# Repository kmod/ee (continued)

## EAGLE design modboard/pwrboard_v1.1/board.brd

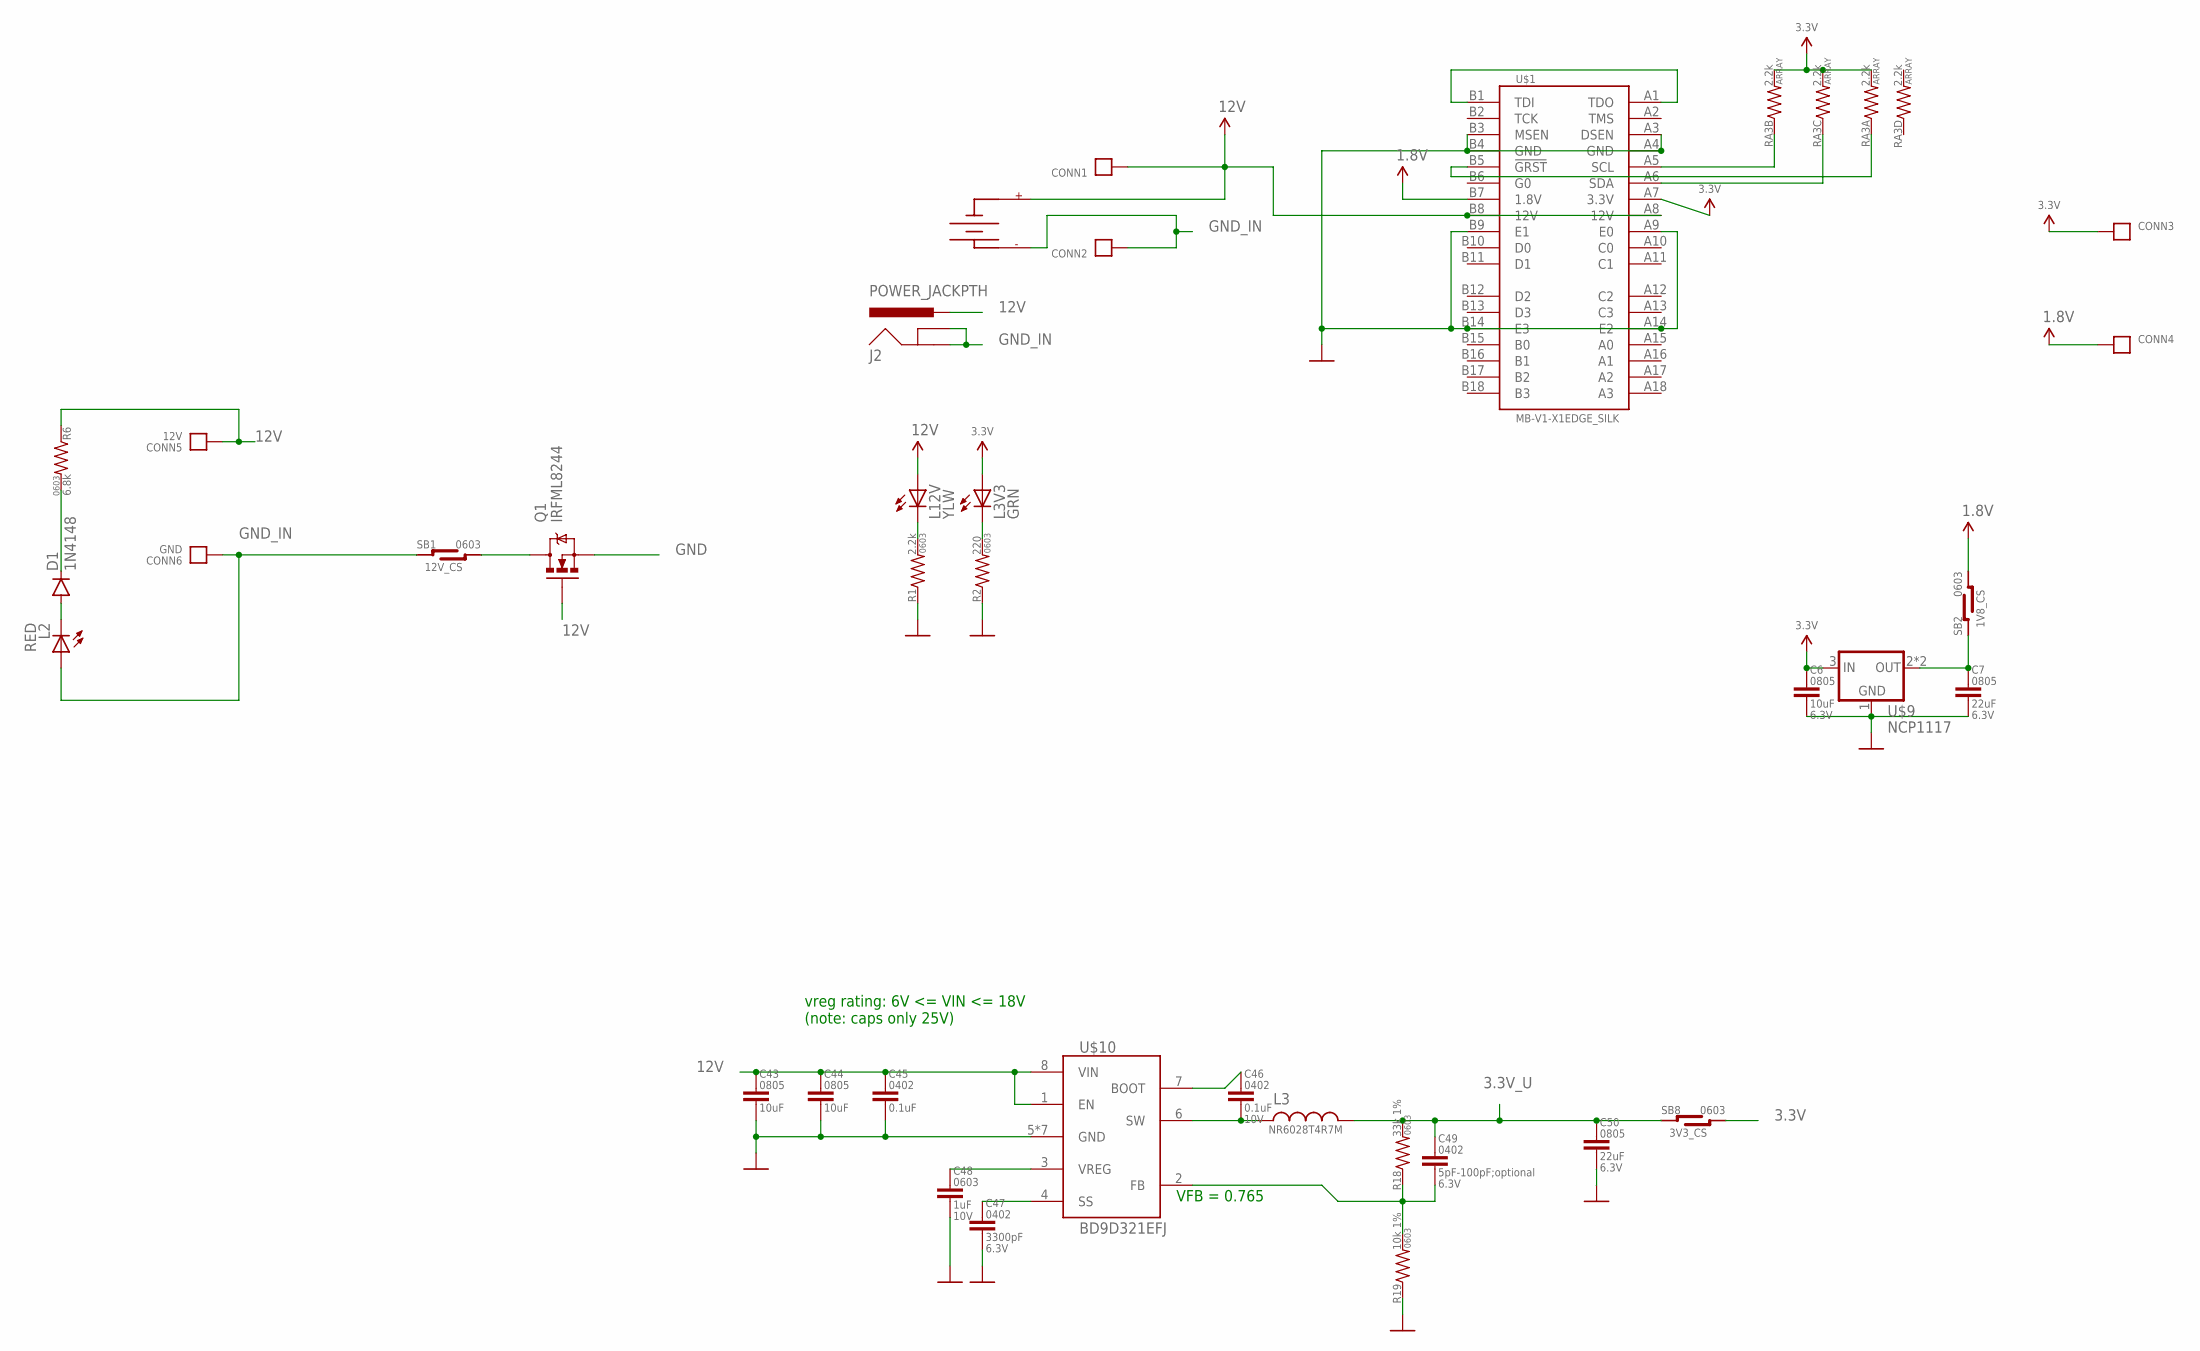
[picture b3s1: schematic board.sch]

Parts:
C6: 10uF; 0805-CAP
C7, C50: 22uF; 0805-CAP
C43, C44: 10uF; 0805-CAP; VOLTAGE 25V
C45: 0.1uF; 0402-CAP; VOLTAGE 25V
C46: 0.1uF; 0402-CAP; VOLTAGE 10V
C47: 3300pF; 0402-CAP
C48: 1uF; 0603-CAP; VOLTAGE 10V
C49: 5pF-100pF;optional; 0402-CAP
CONN1, CONN2, CONN3, CONN4: CONNECTOR18AWG; HOLE_18AWG
CONN5: 12V; SCREW_2.5MM
CONN6: GND; SCREW_2.5MM
D1: 1N4148; SOD-323
J2: POWER_JACKPTH; POWER_JACK_PTH
L2: RED; 0603_LED
L3: NR6028T4R7M; NR60XX
L3V3: GRN; 0603_LED
L12V: YLW; 0603_LED
Q1: IRFML8244; SOT23
R1: 2.2k; 0603-RES
R2: 220; 0603-RES
R6: 6.8k; 0603-RES
R18: 33k 1%; 0603-RES
R19: 10k 1%; 0603-RES
RA3: 2.2k; 0603-ARV
SB1: 12V_CS; SB-0603
SB2: 1V8_CS; SB-0603
SB8: 3V3_CS; SB-0603
U$1: MB-V1-X1EDGE_SILK; MB-V1-X1-EDGE
U$4: SUPPLYPCIE-6-RA; MOLEX_MINIFITJR_6_RA
U$9: NCP1117; SOT223
U$10: BD9D321EFJ; HTSOP8

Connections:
1.8V: CONN4.P$1, SB2.R1, SB2.R2, U$1.B7 (1.8V)
3.3V: C6.1, CONN3.P$1, L3V3.A, RA3.6 (2), RA3.7 (2), RA3.8 (2), SB8.R1, SB8.R2, U$1.A7 (3.3V), U$9.3 (IN)
3.3V_FB: C49.2, R18.1, R19.2, U$10.2 (FB)
3.3V_U: C49.1, C50.1, L3.P$2 (2), R18.2, SB8.L1, SB8.L2
12V: C43.1, C44.1, C45.1, CONN1.P$1, CONN5.P, J2.PWR, L12V.A, Q1.1 (G), R6.1, U$1.A8 (12V), U$1.B8 (12V), U$4.1 (VSUPPLY), U$4.3 (VSUPPLY), U$10.1 (EN), U$10.8 (VIN)
GND: C6.2, C7.2, C43.2, C44.2, C45.2, C47.2, C48.2, C50.2, Q1.2 (S), R1.1, R2.1, R19.1, U$1.A3 (DSEN), U$1.A4 (GND), U$1.A9 (E0), U$1.A14 (E2), U$1.B3 (MSEN), U$1.B4 (GND), U$1.B9 (E1), U$1.B14 (E3), U$9.1 (GND), U$10.5 (GND), U$10.P$1 (GND), U$10.P$2 (GND), U$10.P$3 (GND), U$10.P$4 (GND), U$10.P$5 (GND), U$10.PAD (GND)
GND_IN: CONN2.P$1, CONN6.P, J2.GND, J2.GNDBREAK, L2.A, SB1.L1, SB1.L2, U$4.4 (GND), U$4.6 (GND)
unnamed: L12V.C, R1.2
unnamed: C7.1, SB2.L1, SB2.L2, U$9.2 (OUT), U$9.4 (OUT)
unnamed: L3V3.C, R2.2
unnamed: RA3.3 (1), U$1.A6 (SDA)
unnamed: Q1.3 (D), SB1.R1, SB1.R2
unnamed: D1.C, R6.2
unnamed: RA3.2 (1), U$1.A5 (SCL)
unnamed: RA3.1, U$1.B5 (!GRST)
unnamed: D1.A, L2.C
unnamed: C46.2, L3.P$1 (1), U$10.6 (SW)
unnamed: C46.1, U$10.7 (BOOT)
unnamed: C48.1, U$10.3 (VREG)
unnamed: C47.1, U$10.4 (SS)
TDI: U$1.A1 (TDO), U$1.B1 (TDI)

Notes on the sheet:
VFB = 0.765
vreg rating: 6V <= VIN <= 18V (note: caps only 25V)

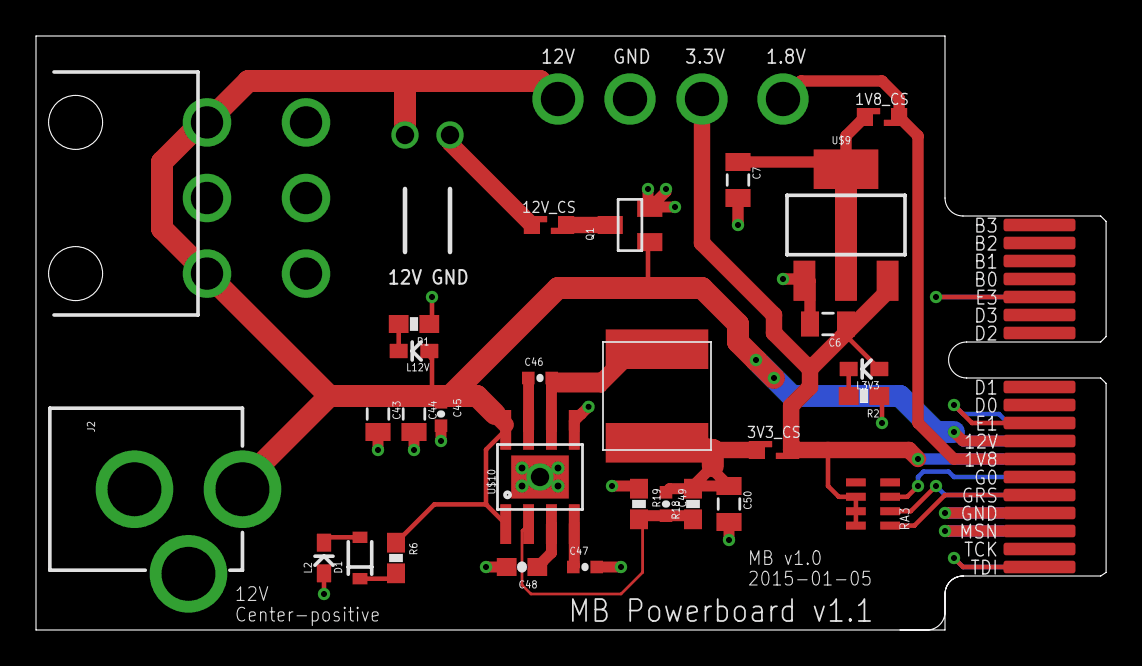
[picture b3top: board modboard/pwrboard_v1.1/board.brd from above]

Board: 2 copper layers, 59.4 x 33.0 mm, 36 parts (0 on the bottom side), 21 nets.

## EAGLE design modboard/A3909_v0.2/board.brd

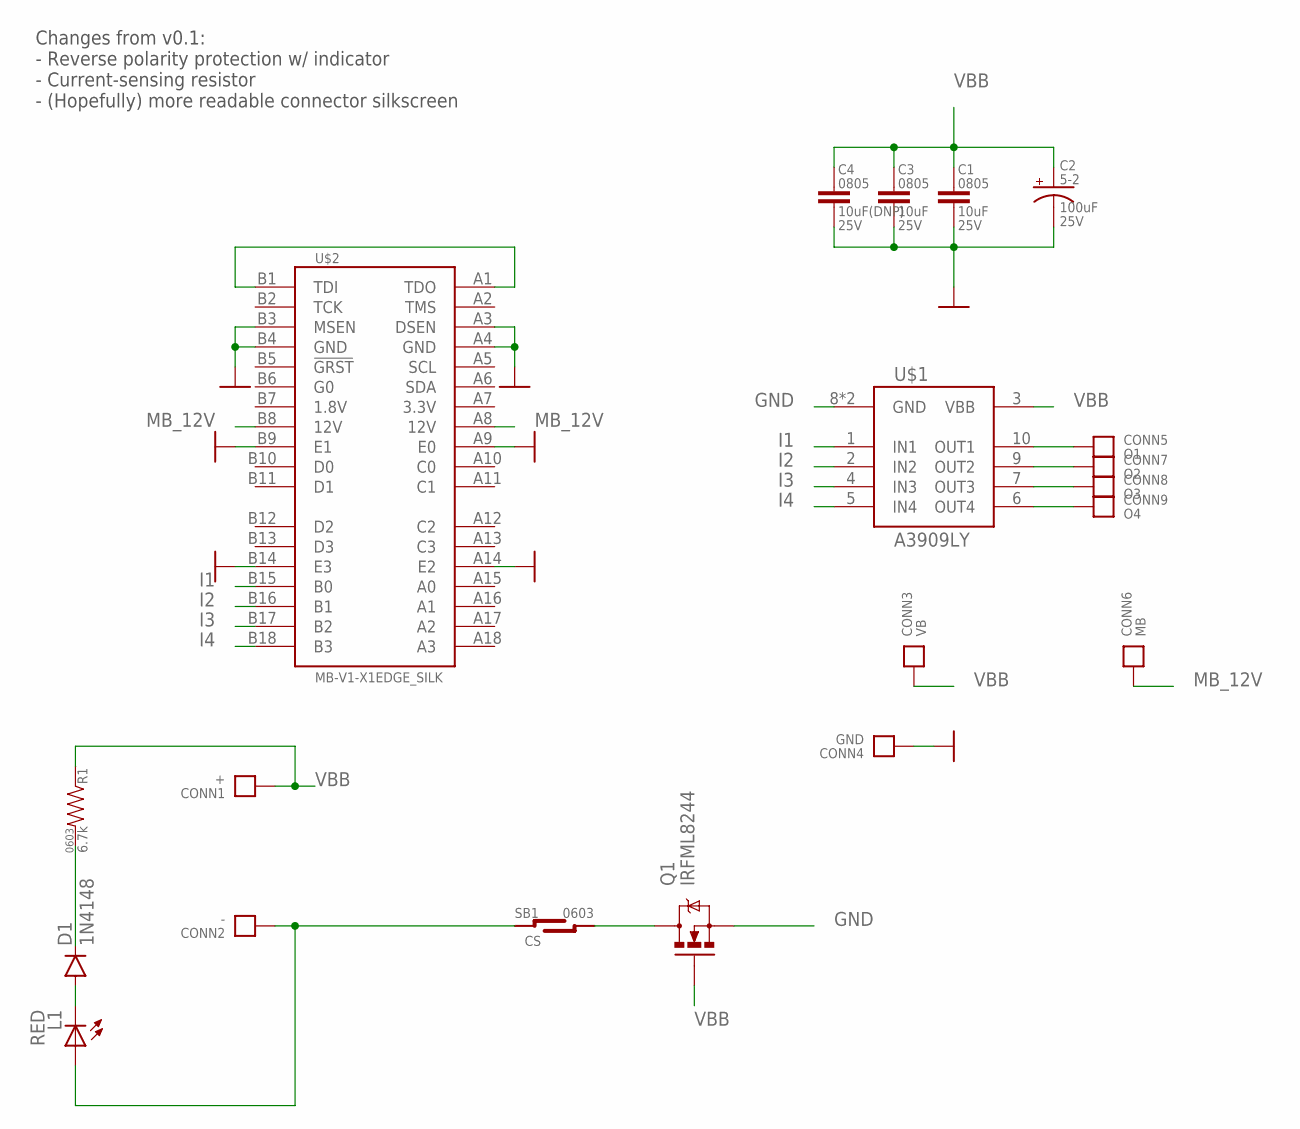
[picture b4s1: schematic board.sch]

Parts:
C1, C3: 10uF; 0805-CAP; VOLTAGE 25V
C2: 100uF; CAP-5-2; VOLTAGE 25V
C4: 10uF(DNP); 0805-CAP; VOLTAGE 25V
CONN1: +; SCREW_5MM
CONN2: -; SCREW_5MM
CONN3: VB; SCREW_2.5MM
CONN4: GND; SCREW_2.5MM
CONN5: O1; SCREW_2.5MM
CONN6: MB; SCREW_2.5MM
CONN7: O2; SCREW_2.5MM
CONN8: O3; SCREW_2.5MM
CONN9: O4; SCREW_2.5MM
D1: 1N4148; SOD-323
L1: RED; 0603_LED
Q1: IRFML8244; SOT23
R1: 6.7k; 0603-RES
SB1: CS; SB-0603
U$1: A3909LY; MSOP10
U$2: MB-V1-X1EDGE_SILK; MB-V1-X1-EDGE

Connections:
GND: C1.2, C2.2 (-), C3.2, C4.2, CONN4.P, Q1.2 (S), U$1.8 (GND), U$1.PAD (GND), U$2.A3 (DSEN), U$2.A4 (GND), U$2.A9 (E0), U$2.A14 (E2), U$2.B3 (MSEN), U$2.B4 (GND), U$2.B9 (E1), U$2.B14 (E3)
I1: U$1.1 (IN1), U$2.B15 (B0)
I2: U$1.2 (IN2), U$2.B16 (B1)
I3: U$1.4 (IN3), U$2.B17 (B2)
I4: U$1.5 (IN4), U$2.B18 (B3)
MB_12V: CONN6.P, U$2.A8 (12V), U$2.B8 (12V)
unnamed: U$2.A1 (TDO), U$2.B1 (TDI)
unnamed: D1.A, L1.C
unnamed: CONN2.P$1, L1.A, SB1.L1, SB1.L2
unnamed: Q1.3 (D), SB1.R1, SB1.R2
unnamed: D1.C, R1.2
O1: CONN5.P, U$1.10 (OUT1)
O2: CONN7.P, U$1.9 (OUT2)
O3: CONN8.P, U$1.7 (OUT3)
O4: CONN9.P, U$1.6 (OUT4)
VBB: C1.1, C2.1 (+), C3.1, C4.1, CONN1.P$1, CONN3.P, Q1.1 (G), R1.1, U$1.3 (VBB)

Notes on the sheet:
Changes from v0.1: - Reverse polarity protection w/ indicator - Current-sensing resistor - (Hopefully) more readable connector silkscreen

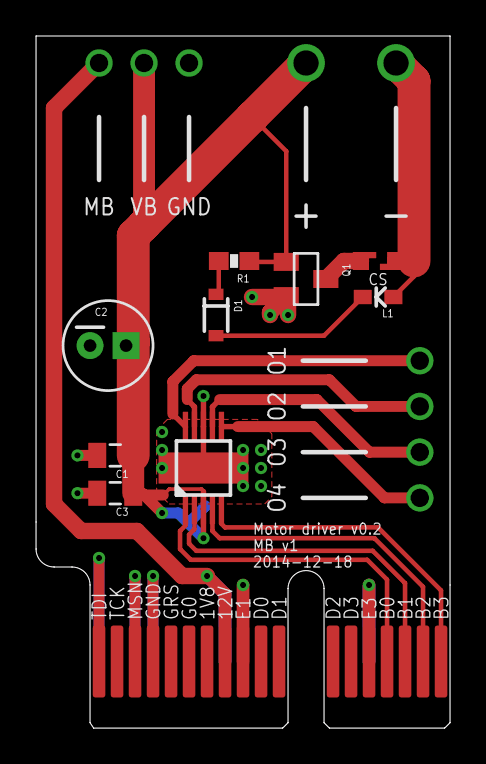
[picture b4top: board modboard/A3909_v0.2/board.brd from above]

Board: 2 copper layers, 23.0 x 38.4 mm, 20 parts (1 on the bottom side), 16 nets.

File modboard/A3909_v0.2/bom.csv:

"Qty";"Value";"Device";"Package";"Parts";"Description";"PACKAGE";"PROD_ID";"VOLTAGE";
"1";"+";"CONNECTORSCREW_5MM";"SCREW_5MM";"CONN1";"Collection of holes/pads for testing/connecting";"";"";"";
"1";"-";"CONNECTORSCREW_5MM";"SCREW_5MM";"CONN2";"Collection of holes/pads for testing/connecting";"";"";"";
"1";"100uF";"CAP_POLPTH-5-2";"CAP-5-2";"C2";"Capacitor Polarized";"5-2";"";"25V";
"2";"10uF";"CAP0805";"0805-CAP";"C1, C3";"Capacitor";"0805";"";"25V";
"1";"10uF(DNP)";"CAP0805";"0805-CAP";"C4";"Capacitor";"0805";"";"25V";
"1";"1N4148";"DIODESOD";"SOD-323";"D1";"Diode";"";"DIO-09646";"";
"1";"6.7k";"RESISTOR0603";"0603-RES";"R1";"Resistor";"0603";"";"";
"1";"A3909LY";"A3909LY";"MSOP10";"U$1";"A3909 Dual Fuul Bridge Motor Driver";"";"";"";
"1";"CS";"SOLDER-BRIDGE0603";"SB-0603";"SB1";"";"0603";"";"";
"1";"GND";"CONNECTORSCREW_2.5MM";"SCREW_2.5MM";"CONN4";"Collection of holes/pads for testing/connecting";"";"";"";
"1";"IRFML8244";"MOSFET-NCHANNELBSS138";"SOT23";"Q1";"Common NMOSFET Parts";"";"TRANS-00830";"";
"1";"MB";"CONNECTORSCREW_2.5MM";"SCREW_2.5MM";"CONN6";"Collection of holes/pads for testing/connecting";"";"";"";
"1";"MB-V1-X1EDGE_SILK";"MB-V1-X1EDGE_SILK";"MB-V1-X1-EDGE";"U$2";"";"";"";"";
"1";"O1";"CONNECTORSCREW_2.5MM";"SCREW_2.5MM";"CONN5";"Collection of holes/pads for testing/connecting";"";"";"";
"1";"O2";"CONNECTORSCREW_2.5MM";"SCREW_2.5MM";"CONN7";"Collection of holes/pads for testing/connecting";"";"";"";
"1";"O3";"CONNECTORSCREW_2.5MM";"SCREW_2.5MM";"CONN8";"Collection of holes/pads for testing/connecting";"";"";"";
"1";"O4";"CONNECTORSCREW_2.5MM";"SCREW_2.5MM";"CONN9";"Collection of holes/pads for testing/connecting";"";"";"";
"1";"RED";"LED0603";"0603_LED";"L1";"";"";"";"";
"1";"VB";"CONNECTORSCREW_2.5MM";"SCREW_2.5MM";"CONN3";"Collection of holes/pads for testing/connecting";"";"";"";

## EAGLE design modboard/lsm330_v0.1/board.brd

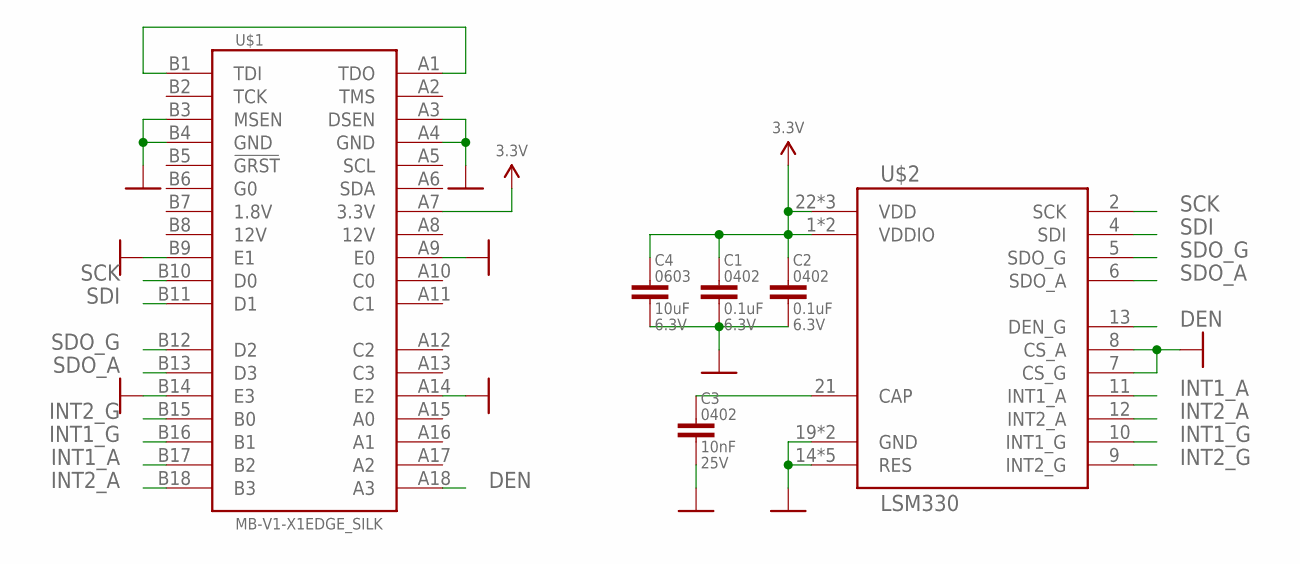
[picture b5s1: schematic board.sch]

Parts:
C1, C2: 0.1uF; 0402-CAP
C3: 10nF; 0402-CAP; VOLTAGE 25V
C4: 10uF; 0603-CAP
U$1: MB-V1-X1EDGE_SILK; MB-V1-X1-EDGE
U$2: LSM330

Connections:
3.3V: C1.1, C2.1, C4.1, U$1.A7 (3.3V), U$2.1 (VDDIO), U$2.3 (VDDIO), U$2.22 (VDD), U$2.23 (VDD), U$2.24 (VDD)
CAP: C3.1, U$2.21 (CAP)
DEN: U$1.A18 (A3), U$2.13 (DEN_G)
GND: C1.2, C2.2, C3.2, C4.2, U$1.A3 (DSEN), U$1.A4 (GND), U$1.A9 (E0), U$1.A14 (E2), U$1.B3 (MSEN), U$1.B4 (GND), U$1.B9 (E1), U$1.B14 (E3), U$2.7 (CS_G), U$2.8 (CS_A), U$2.14 (RES), U$2.15 (RES), U$2.16 (RES), U$2.17 (RES), U$2.18 (RES), U$2.19 (GND), U$2.20 (GND)
INT1_A: U$1.B17 (B2), U$2.11 (INT1_A)
INT1_G: U$1.B16 (B1), U$2.10 (INT1_G)
INT2_A: U$1.B18 (B3), U$2.12 (INT2_A)
INT2_G: U$1.B15 (B0), U$2.9 (INT2_G)
unnamed: U$1.A1 (TDO), U$1.B1 (TDI)
SCK: U$1.B10 (D0), U$2.2 (SCK)
SDI: U$1.B11 (D1), U$2.4 (SDI)
SDO_A: U$1.B13 (D3), U$2.6 (SDO_A)
SDO_G: U$1.B12 (D2), U$2.5 (SDO_G)

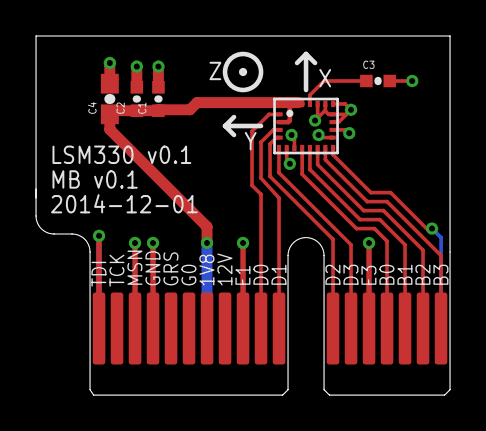
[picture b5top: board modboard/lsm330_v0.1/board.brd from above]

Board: 2 copper layers, 23.0 x 19.9 mm, 6 parts (0 on the bottom side), 13 nets.

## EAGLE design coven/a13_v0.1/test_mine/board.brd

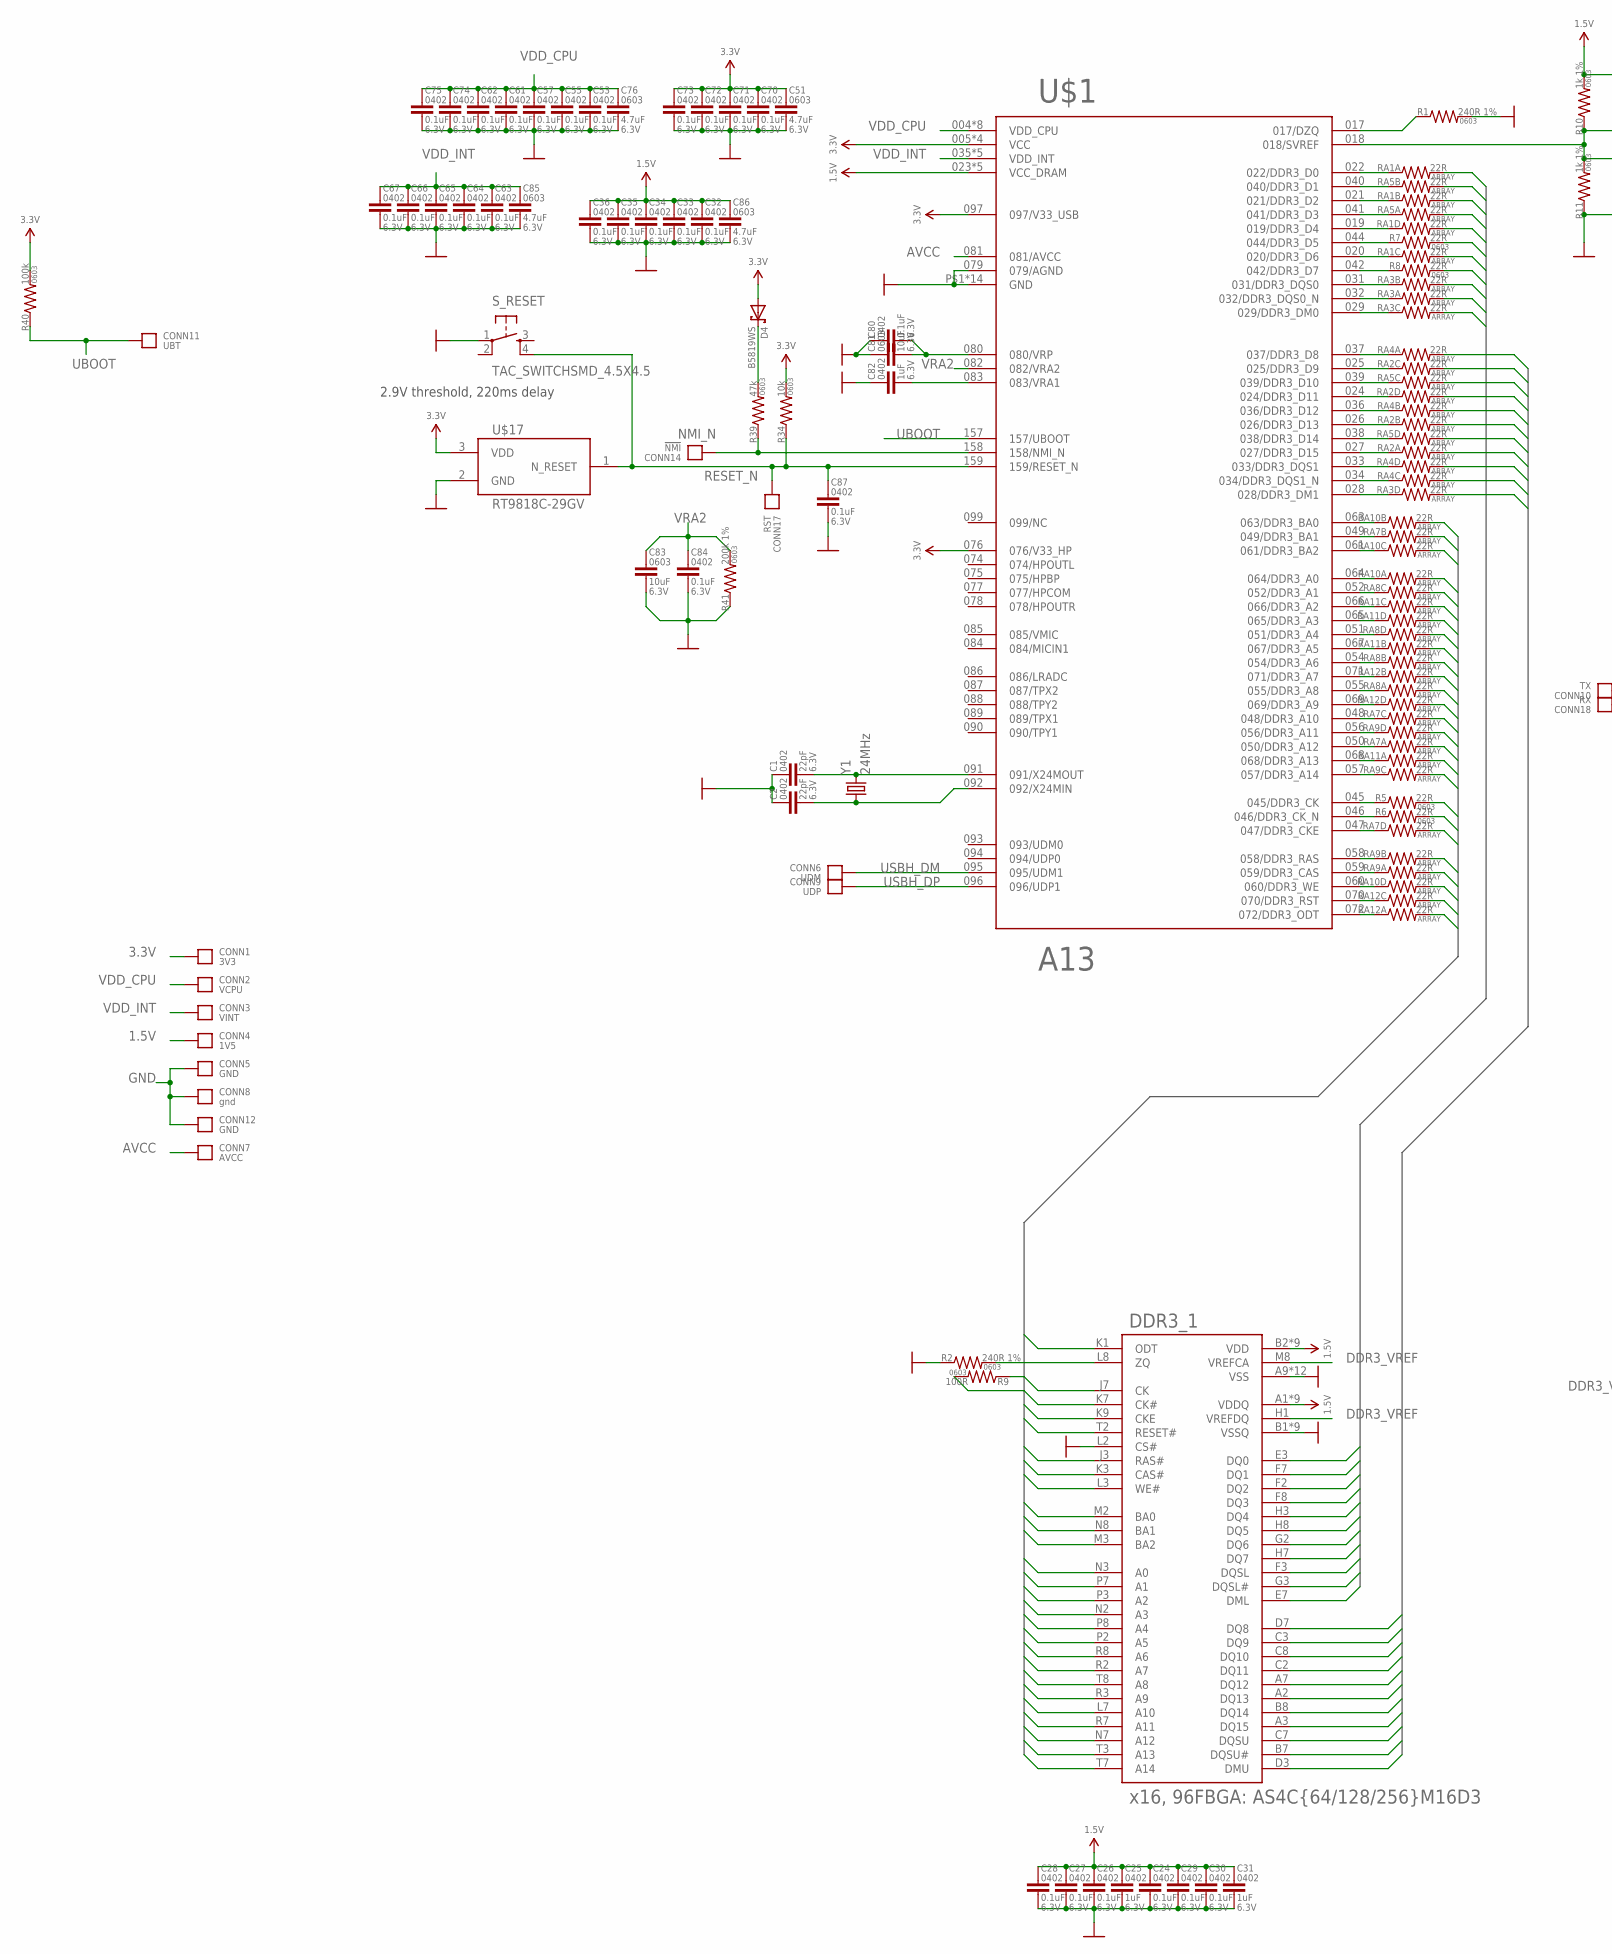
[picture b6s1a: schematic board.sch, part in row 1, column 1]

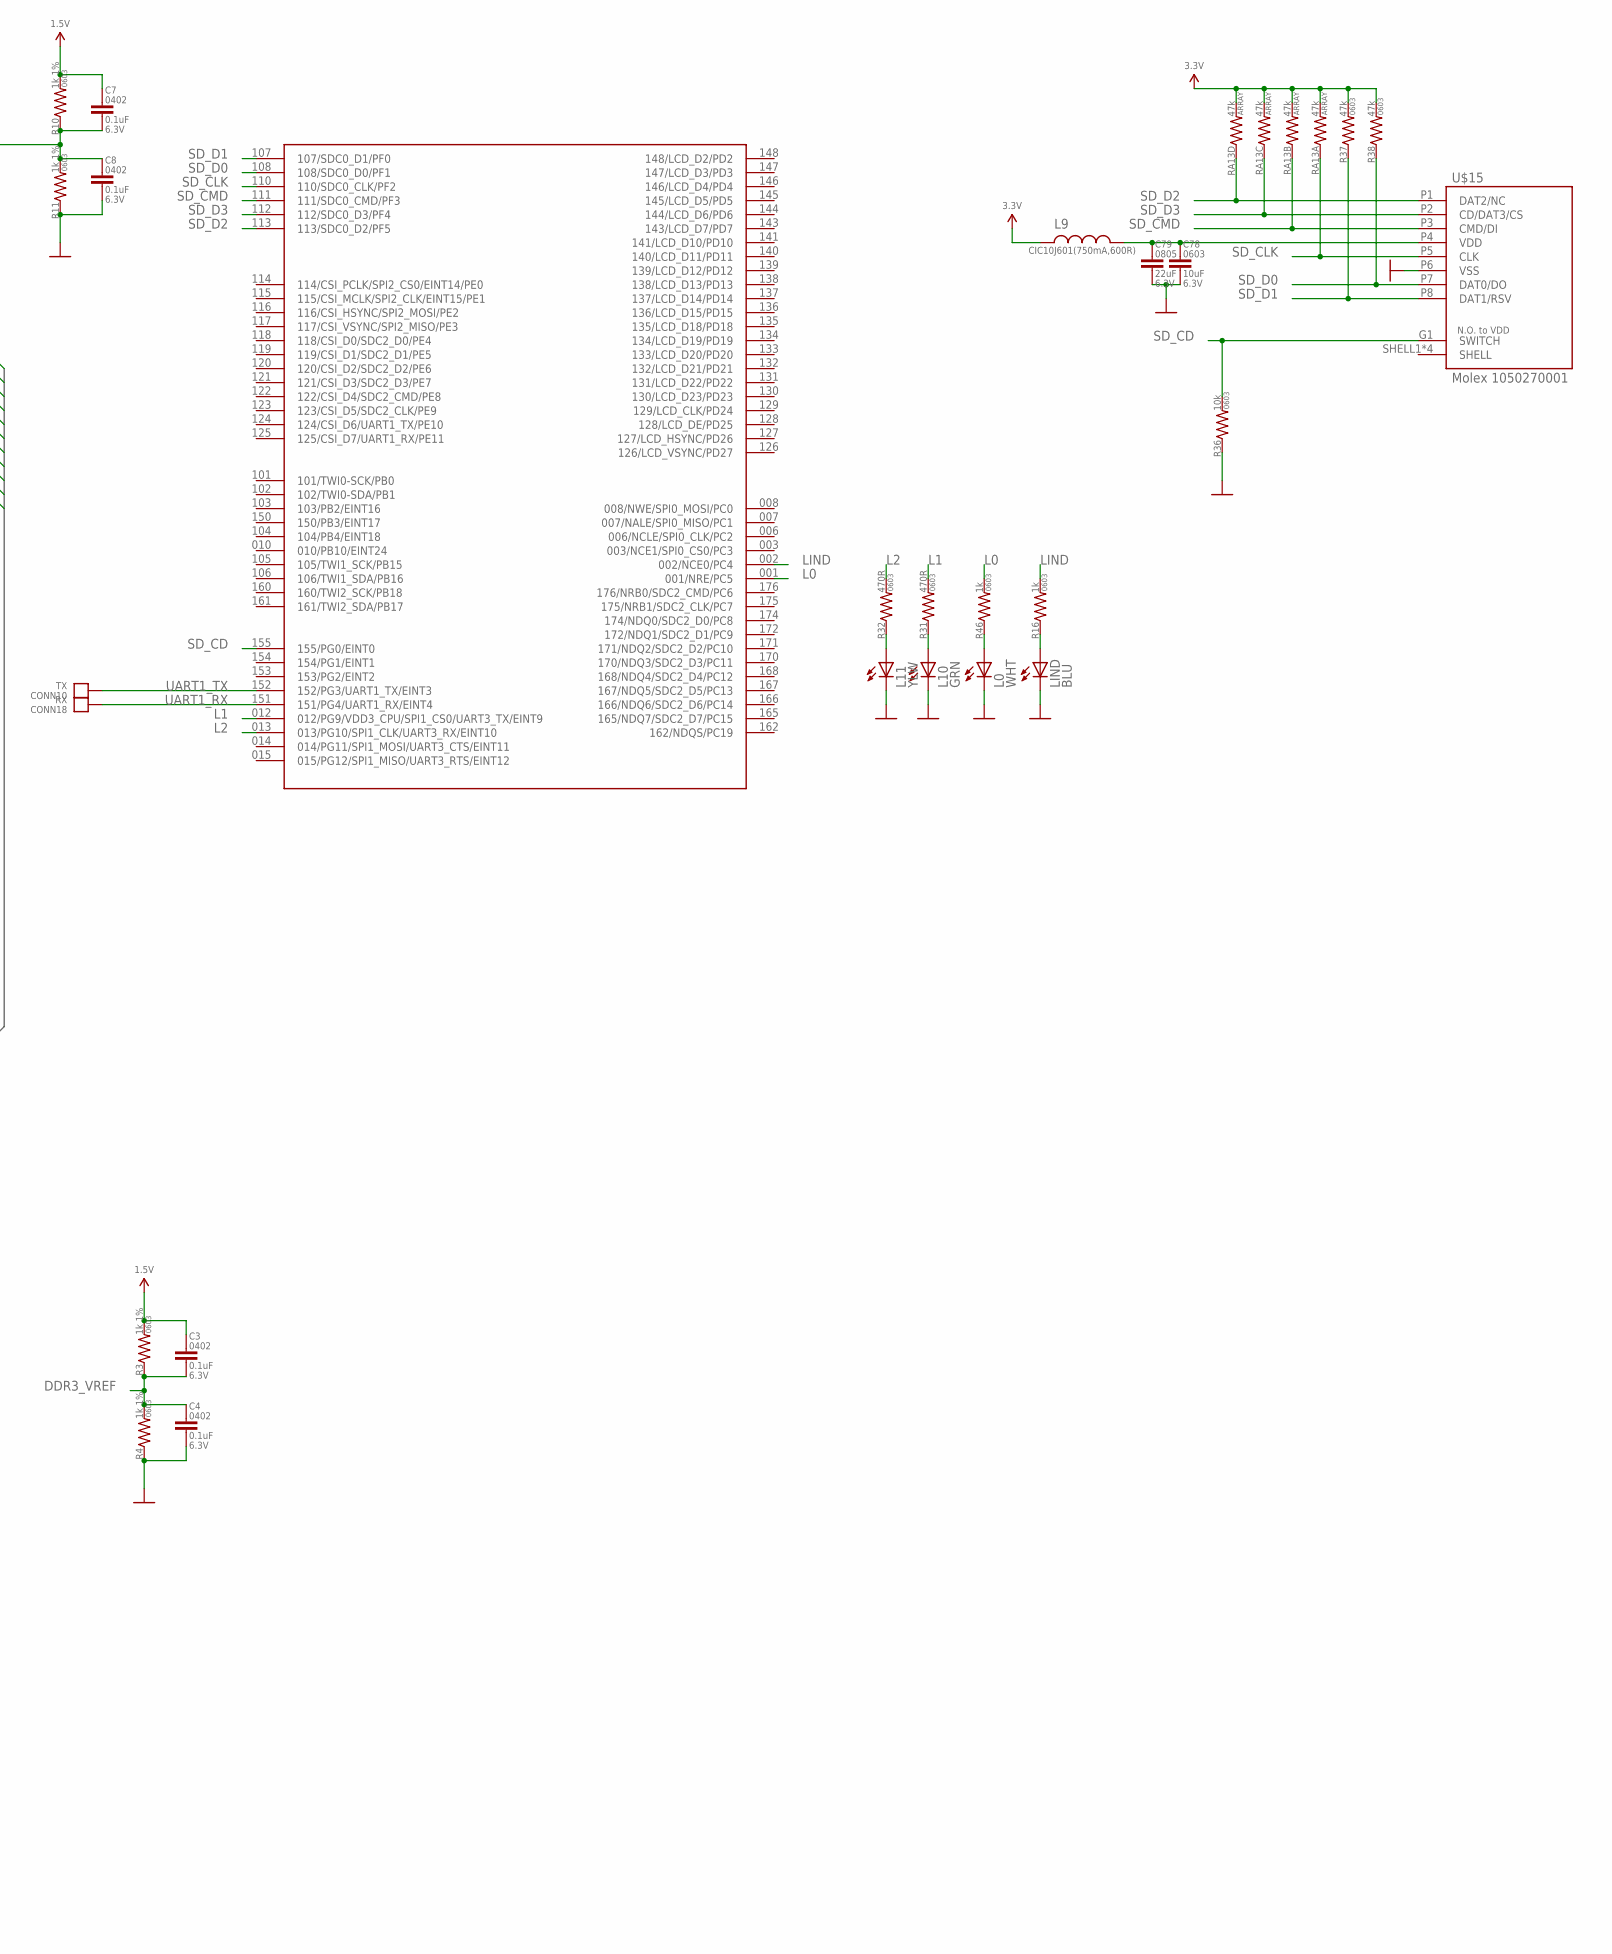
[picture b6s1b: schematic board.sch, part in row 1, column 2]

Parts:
C1, C2: 22pF; 0402-CAP
C3, C4, C7, C8, C24, C26, C27, C28, C29, C30, C32, C33, C34, C35, C36, C53, C55, C57, C61, C62, C63, C64, C65, C66, C67, C70, C71, C72, C73, C74, C75, C80, C84, C87: 0.1uF; 0402-CAP
C25, C31, C82: 1uF; 0402-CAP
C51, C76, C85, C86: 4.7uF; 0603-CAP
C78, C81, C83: 10uF; 0603-CAP
C79: 22uF; 0805-CAP
CONN1: 3V3; HOLE_22AWG
CONN2: VCPU; HOLE_22AWG
CONN3: VINT; HOLE_22AWG
CONN4: 1V5; HOLE_22AWG
CONN5, CONN12: GND; HOLE_22AWG
CONN6: UDM; HOLE_22AWG
CONN7: AVCC; HOLE_22AWG
CONN8: gnd; CLIP-AREA
CONN9: UDP; HOLE_22AWG
CONN10: TX; HOLE_22AWG
CONN11: UBT; HOLE_22AWG
CONN14: !NMI; HOLE_22AWG
CONN17: RST; HOLE_22AWG
CONN18: RX; HOLE_22AWG
D4: B5819WS; SOD-323
DDR3_1: x16, 96FBGA: AS4C{64/128/256}M16D3; BGA96
L0: WHT; 0603_LED
L9: CIC10J601(750mA,600R); 0603
L10: GRN; 0603_LED
L11: YLW; 0603_LED
LIND: BLU; 0603_LED
R1, R2: 240R 1%; 0603-RES
R3, R4, R10, R11: 1k 1%; 0603-RES
R5, R6, R7, R8: 22R; 0603-RES
R9: 100R; 0603-RES
R16, R46: 1k; 0603-RES
R31, R32: 470R; 0603-RES
R34, R36: 10k; 0603-RES
R37, R38, R39: 47k; 0603-RES
R40: 100k; 0603-RES
R41: 200k 1%; 0603-RES
RA1, RA2, RA3, RA4, RA5, RA7, RA8, RA9, RA10, RA11, RA12: 22R; 0603-ARV
RA13: 47k; 0603-ARV
S_RESET: TAC_SWITCHSMD_4.5X4.5; TAC_SWITCH_SMD_4.5X4.5
U$1: A13; TQFP176_0.4
U$15: Molex 1050270001; MICROSD-MOLEX-1050270001
U$17: RT9818C-29GV; SOT23-3
Y1: 24MHz; HC49US

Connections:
1.5V: C3.1, C7.1, C24.1, C25.1, C26.1, C27.1, C28.1, C29.1, C30.1, C31.1, C32.1, C33.1, C34.1, C35.1, C36.1, C86.1, CONN4.P, DDR3_1.A1 (VDDQ), DDR3_1.A8 (VDDQ), DDR3_1.B2 (VDD), DDR3_1.C1 (VDDQ), DDR3_1.C9 (VDDQ), DDR3_1.D2 (VDDQ), DDR3_1.D9 (VDD), DDR3_1.E9 (VDDQ), DDR3_1.F1 (VDDQ), DDR3_1.G7 (VDD), DDR3_1.H2 (VDDQ), DDR3_1.H9 (VDDQ), DDR3_1.K2 (VDD), DDR3_1.K8 (VDD), DDR3_1.N1 (VDD), DDR3_1.N9 (VDD), DDR3_1.R1 (VDD), DDR3_1.R9 (VDD), R3.2, R10.2, U$1.023 (VCC_DRAM), U$1.030 (VCC_DRAM), U$1.043 (VCC_DRAM), U$1.053 (VCC_DRAM), U$1.062 (VCC_DRAM)
3.3V: C51.1, C70.1, C71.1, C72.1, C73.1, CONN1.P, D4.A, L9.1, R34.2, R37.2, R38.2, R40.2, RA13.5 (2), RA13.6 (2), RA13.7 (2), RA13.8 (2), U$1.005 (VCC), U$1.076 (076/V33_HP), U$1.097 (097/V33_USB), U$1.100 (VCC), U$1.142 (VCC), U$1.163 (VCC), U$17.3 (VDD)
AVCC: CONN7.P, U$1.081 (081/AVCC)
DDR3_A0: DDR3_1.N3 (A0), RA10.8 (2)
DDR3_A1: DDR3_1.P7 (A1), RA8.6 (2)
DDR3_A2: DDR3_1.P3 (A2), RA11.6 (2)
DDR3_A3: DDR3_1.N2 (A3), RA11.5 (2)
DDR3_A4: DDR3_1.P8 (A4), RA8.5 (2)
DDR3_A5: DDR3_1.P2 (A5), RA11.7 (2)
DDR3_A6: DDR3_1.R8 (A6), RA8.7 (2)
DDR3_A7: DDR3_1.R2 (A7), RA12.7 (2)
DDR3_A8: DDR3_1.T8 (A8), RA8.8 (2)
DDR3_A9: DDR3_1.R3 (A9), RA12.5 (2)
DDR3_A10: DDR3_1.L7 (A10), RA7.6 (2)
DDR3_A11: DDR3_1.R7 (A11), RA9.5 (2)
DDR3_A12: DDR3_1.N7 (A12), RA7.8 (2)
DDR3_A13: DDR3_1.T3 (A13), RA11.8 (2)
DDR3_A14: DDR3_1.T7 (A14), RA9.6 (2)
DDR3_BA0: DDR3_1.M2 (BA0), RA10.7 (2)
DDR3_BA1: DDR3_1.N8 (BA1), RA7.7 (2)
DDR3_BA2: DDR3_1.M3 (BA2), RA10.6 (2)
DDR3_CAS: DDR3_1.K3 (CAS#), RA9.8 (2)
DDR3_CK: DDR3_1.J7 (CK), R5.2, R9.1
DDR3_CK#: DDR3_1.K7 (CK#), R6.2, R9.2
DDR3_CKE: DDR3_1.K9 (CKE), RA7.5 (2)
DDR3_DML: DDR3_1.E7 (DML), RA3.6 (2)
DDR3_DMU: DDR3_1.D3 (DMU), RA3.5 (2)
DDR3_DQ0: DDR3_1.E3 (DQ0), RA1.8 (2)
DDR3_DQ1: DDR3_1.F7 (DQ1), RA5.7 (2)
DDR3_DQ2: DDR3_1.F2 (DQ2), RA1.7 (2)
DDR3_DQ3: DDR3_1.F8 (DQ3), RA5.8 (2)
DDR3_DQ4: DDR3_1.H3 (DQ4), RA1.5 (2)
DDR3_DQ5: DDR3_1.H8 (DQ5), R7.2
DDR3_DQ6: DDR3_1.G2 (DQ6), RA1.6 (2)
DDR3_DQ7: DDR3_1.H7 (DQ7), R8.2
DDR3_DQ8: DDR3_1.D7 (DQ8), RA4.8 (2)
DDR3_DQ9: DDR3_1.C3 (DQ9), RA2.6 (2)
DDR3_DQ10: DDR3_1.C8 (DQ10), RA5.6 (2)
DDR3_DQ11: DDR3_1.C2 (DQ11), RA2.5 (2)
DDR3_DQ12: DDR3_1.A7 (DQ12), RA4.7 (2)
DDR3_DQ13: DDR3_1.A2 (DQ13), RA2.7 (2)
DDR3_DQ14: DDR3_1.B8 (DQ14), RA5.5 (2)
DDR3_DQ15: DDR3_1.A3 (DQ15), RA2.8 (2)
DDR3_DQSL: DDR3_1.F3 (DQSL), RA3.7 (2)
DDR3_DQSL#: DDR3_1.G3 (DQSL#), RA3.8 (2)
DDR3_DQSU: DDR3_1.C7 (DQSU), RA4.5 (2)
DDR3_DQSU#: DDR3_1.B7 (DQSU#), RA4.6 (2)
DDR3_ODT: DDR3_1.K1 (ODT), RA12.8 (2)
DDR3_RAS: DDR3_1.J3 (RAS#), RA9.7 (2)
DDR3_RST: DDR3_1.T2 (RESET#), RA12.6 (2)
DDR3_VREF: C3.2, C4.1, DDR3_1.H1 (VREFDQ), DDR3_1.M8 (VREFCA), R3.1, R4.2
DDR3_WE: DDR3_1.L3 (WE#), RA10.5 (2)
GND: C1.1, C2.1, C4.2, C8.2, C24.2, C25.2, C26.2, C27.2, C28.2, C29.2, C30.2, C31.2, C32.2, C33.2, C34.2, C35.2, C36.2, C51.2, C53.2, C55.2, C57.2, C61.2, C62.2, C63.2, C64.2, C65.2, C66.2, C67.2, C70.2, C71.2, C72.2, C73.2, C74.2, C75.2, C76.2, C78.2, C79.2, C80.1, C81.1, C82.1, C83.2, C84.2, C85.2, C86.2, C87.2, CONN5.P, CONN8.P$1, CONN8.P$2, CONN12.P, DDR3_1.A9 (VSS), DDR3_1.B1 (VSSQ), DDR3_1.B3 (VSS), DDR3_1.B9 (VSSQ), DDR3_1.D1 (VSSQ), DDR3_1.D8 (VSSQ), DDR3_1.E1 (VSS), DDR3_1.E2 (VSSQ), DDR3_1.E8 (VSSQ), DDR3_1.F9 (VSSQ), DDR3_1.G1 (VSSQ), DDR3_1.G8 (VSS), DDR3_1.G9 (VSSQ), DDR3_1.J2 (VSS), DDR3_1.J8 (VSS), DDR3_1.L2 (CS#), DDR3_1.M1 (VSS), DDR3_1.M9 (VSS), DDR3_1.P1 (VSS), DDR3_1.P9 (VSS), DDR3_1.T1 (VSS), DDR3_1.T9 (VSS), L0.C, L10.C, L11.C, LIND.C, R1.2, R2.1, R4.1, R11.1, R36.1, R41.1, S_RESET.1, U$1.079 (079/AGND), U$1.P$1 (GND), U$1.P$2 (GND), U$1.P$3 (GND), U$1.P$4 (GND), U$1.P$5 (GND), U$1.P$6 (GND), U$1.P$7 (GND), U$1.P$8 (GND), U$1.P$9 (GND), U$1.P$10 (GND), U$1.P$11 (GND), U$1.P$12 (GND), U$1.P$13 (GND), U$1.PAD (GND), U$15.P6 (VSS), U$17.2 (GND)
L0: R46.2, U$1.001 (001/NRE/PC5)
L1: R31.2, U$1.012 (012/PG9/VDD3_CPU/SPI1_CS0/UART3_TX/EINT9)
L2: R32.2, U$1.013 (013/PG10/SPI1_CLK/UART3_RX/EINT10)
LIND: R16.2, U$1.002 (002/NCE0/PC4)
unnamed: R1.1, U$1.017 (017/DZQ)
unnamed: RA1.3 (1), U$1.020 (020/DDR3_D6)
unnamed: C1.2, U$1.091 (091/X24MOUT), Y1.2
unnamed: C2.2, U$1.092 (092/X24MIN), Y1.1
unnamed: RA1.4 (1), U$1.019 (019/DDR3_D4)
unnamed: DDR3_1.L8 (ZQ), R2.2
unnamed: RA3.4 (1), U$1.028 (028/DDR3_DM1)
unnamed: RA4.3 (1), U$1.034 (034/DDR3_DQS1_N)
unnamed: RA4.4 (1), U$1.033 (033/DDR3_DQS1)
unnamed: RA2.1, U$1.027 (027/DDR3_D15)
unnamed: RA5.4 (1), U$1.038 (038/DDR3_D14)
unnamed: RA2.2 (1), U$1.026 (026/DDR3_D13)
unnamed: RA4.2 (1), U$1.036 (036/DDR3_D12)
unnamed: RA2.4 (1), U$1.024 (024/DDR3_D11)
unnamed: RA5.3 (1), U$1.039 (039/DDR3_D10)
unnamed: RA2.3 (1), U$1.025 (025/DDR3_D9)
unnamed: RA4.1, U$1.037 (037/DDR3_D8)
unnamed: RA3.3 (1), U$1.029 (029/DDR3_DM0)
unnamed: RA3.1, U$1.032 (032/DDR3_DQS0_N)
unnamed: RA3.2 (1), U$1.031 (031/DDR3_DQS0)
unnamed: R8.1, U$1.042 (042/DDR3_D7)
unnamed: R7.1, U$1.044 (044/DDR3_D5)
unnamed: RA5.1, U$1.041 (041/DDR3_D3)
unnamed: RA1.2 (1), U$1.021 (021/DDR3_D2)
unnamed: RA5.2 (1), U$1.040 (040/DDR3_D1)
unnamed: RA1.1, U$1.022 (022/DDR3_D0)
unnamed: RA10.2 (1), U$1.063 (063/DDR3_BA0)
unnamed: RA7.2 (1), U$1.049 (049/DDR3_BA1)
unnamed: RA10.3 (1), U$1.061 (061/DDR3_BA2)
unnamed: RA10.1, U$1.064 (064/DDR3_A0)
unnamed: RA8.3 (1), U$1.052 (052/DDR3_A1)
unnamed: RA11.3 (1), U$1.066 (066/DDR3_A2)
unnamed: RA11.4 (1), U$1.065 (065/DDR3_A3)
unnamed: RA8.4 (1), U$1.051 (051/DDR3_A4)
unnamed: RA11.2 (1), U$1.067 (067/DDR3_A5)
unnamed: RA8.2 (1), U$1.054 (054/DDR3_A6)
unnamed: RA12.2 (1), U$1.071 (071/DDR3_A7)
unnamed: RA8.1, U$1.055 (055/DDR3_A8)
unnamed: RA12.4 (1), U$1.069 (069/DDR3_A9)
unnamed: RA7.3 (1), U$1.048 (048/DDR3_A10)
unnamed: RA9.4 (1), U$1.056 (056/DDR3_A11)
unnamed: RA7.1, U$1.050 (050/DDR3_A12)
unnamed: RA11.1, U$1.068 (068/DDR3_A13)
unnamed: RA9.3 (1), U$1.057 (057/DDR3_A14)
unnamed: R5.1, U$1.045 (045/DDR3_CK)
unnamed: R6.1, U$1.046 (046/DDR3_CK_N)
unnamed: RA7.4 (1), U$1.047 (047/DDR3_CKE)
unnamed: RA9.2 (1), U$1.058 (058/DDR3_RAS)
unnamed: RA9.1, U$1.059 (059/DDR3_CAS)
unnamed: RA10.4 (1), U$1.060 (060/DDR3_WE)
unnamed: RA12.3 (1), U$1.070 (070/DDR3_RST)
unnamed: RA12.1, U$1.072 (072/DDR3_ODT)
unnamed: LIND.A, R16.1
unnamed: L10.A, R31.1
unnamed: L11.A, R32.1
unnamed: D4.C, R39.2
unnamed: C78.1, C79.1, L9.2, U$15.P4 (VDD)
unnamed: L0.A, R46.1
NMI_N: CONN14.P, R39.1, U$1.158 (158/NMI_N)
RESET_N: C87.1, CONN17.P, R34.1, S_RESET.4, U$1.159 (159/RESET_N), U$17.1 (N_RESET)
SD_CD: R36.2, U$1.155 (155/PG0/EINT0), U$15.G1 (SWITCH)
SD_CLK: RA13.1, U$1.110 (110/SDC0_CLK/PF2), U$15.P5 (CLK)
SD_CMD: RA13.2 (1), U$1.111 (111/SDC0_CMD/PF3), U$15.P3 (CMD/DI)
SD_D0: R38.1, U$1.108 (108/SDC0_D0/PF1), U$15.P7 (DAT0/DO)
SD_D1: R37.1, U$1.107 (107/SDC0_D1/PF0), U$15.P8 (DAT1/RSV)
SD_D2: RA13.4 (1), U$1.113 (113/SDC0_D2/PF5), U$15.P1 (DAT2/NC)
SD_D3: RA13.3 (1), U$1.112 (112/SDC0_D3/PF4), U$15.P2 (CD/DAT3/CS)
SVREF: C7.2, C8.1, R10.1, R11.2, U$1.018 (018/SVREF)
UART1_RX: CONN18.P, U$1.151 (151/PG4/UART1_RX/EINT4)
UART1_TX: CONN10.P, U$1.152 (152/PG3/UART1_TX/EINT3)
UBOOT: CONN11.P, R40.1, U$1.157 (157/UBOOT)
USBH_DM: CONN6.P, U$1.095 (095/UDM1)
USBH_DP: CONN9.P, U$1.096 (096/UDP1)
VDD_CPU: C53.1, C55.1, C57.1, C61.1, C62.1, C74.1, C75.1, C76.1, CONN2.P, U$1.004 (VDD_CPU), U$1.009 (VDD_CPU), U$1.011 (VDD_CPU), U$1.016 (VDD_CPU), U$1.156 (VDD_CPU), U$1.164 (VDD_CPU), U$1.169 (VDD_CPU), U$1.173 (VDD_CPU)
VDD_INT: C63.1, C64.1, C65.1, C66.1, C67.1, C85.1, CONN3.P, U$1.035 (VDD_INT), U$1.073 (VDD_INT), U$1.098 (VDD_INT), U$1.109 (VDD_INT), U$1.149 (VDD_INT)
VRA1: C82.2, U$1.083 (083/VRA1)
VRA2: C83.1, C84.1, R41.2, U$1.082 (082/VRA2)
VRP: C80.2, C81.2, U$1.080 (080/VRP)

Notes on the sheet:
2.9V threshold, 220ms delay
